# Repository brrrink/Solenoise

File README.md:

# Solenoise

## Overview

Solenoise is an open-source hardware and software system designed to transform everyday objects—such as metal plates, wooden surfaces, or architectural elements—into programmable percussive instruments. By leveraging solenoids as electromagnetic actuators, Solenoise enables automated performance, enhancing musical expressivity and extending human capabilities in experimental music, interactive installations, and architectural sound design.

The resurgence of analog modular synthesis, coupled with advancements in physical computing, has inspired this project. Traditional percussive instruments are limited by their fixed physical properties; Solenoise addresses this by providing a versatile control interface that bridges digital and physical realms.

## Key Features

- **Multi-Modal Input Control**: Supports class-compliant MIDI over TRS Mini-Jack, CV/gate inputs with internal logic for simplified and seamless integration with midi capable devices, modular synthesisers, and sequencers.
- **Hardware Simplicity**: Built around a Teensy 4.0 microcontroller with driverless MIDI input and simplified input protection circuits, ensuring compatibility with external devices.
- **Efficient Actuation**: Uses logic-level MOSFETs and protective transistors for safe and efficient operation of inductive loads (solenoids).
- **Configurable Software**: A flexible framework optimises latency and expressivity, with a focus on CV/Trigger input processing along with class compliant MIDI input.
- **Open-Source Ethos**: Unlike proprietary systems (e.g., Polyend Perc, Dada Machines Automat), Solenoise aims to democratise solenoid augmentation and aims to further collaborative innovation.

## Hardware Requirements

- **Microcontroller**: Teensy 4.0 (required for high-speed processing and MIDI support).
- **Solenoids**: Compatible 12V DC solenoids (e.g., push-pull types for striking objects).
- **Power Supply**: 12VDC Powers the development and the solenoids, with internal voltage protection and rectification.

### Input/Output

- **MIDI**: class-compliant MIDI (TRS Type A) via 3.175mm (1/8 inch) 'Mini Jack' input.
- **CV/Gate**: Analog inputs with protection circuits.

## Installation

- **Clone the repository**: git clone https://github.com/brrrink/Solenoise/solenoise.git
- cd solenoise
- Use Platformio to upload firmware to Teensy 4.0, hardware is available to purchase with pre-mounted SMD components or see the Solenoise Production Files folder, for all production ready design files.
- Upload these design files to the PCB manufacturer of your choice, who should be able to provide full soldered SMD PCB's from these files.
- A small number of through-hole components have to be added, these have been minimised to the degree possible to facilitate ease of construction.

## Usage

### Basic Setup

Attach solenoids to objects (e.g., via 3D-printed mounts—in progress enhancement).

Connect inputs:
- MIDI: Plug into a DAW or MIDI controller.
- Gates: Trigger via digital signals from sequencers.
- CV/Trigger: Use modular synth outputs for voltage-based control.

### Example: MIDI-Controlled Percussion

Send MIDI notes to Solenoise via Mini Jack (Type A).

### CV/Gate Integration

CV input controls the allocation of solenoid (12 in total)

Gate input will trigger discrete strikes, supplemented with MIDI for analog and moblie (battery powered) workflows.

### Performance Evaluation

Latency: <5ms for MIDI/CV processing (tested on Teensy 4.0).

Applications: Experimental music (e.g., hybrid human-robot performances), interactive art (e.g., responsive installations), sound design (e.g., architectural acoustics).

## Comparisons to Existing Systems

Solenoise builds on commercial and academic precedents but emphasises accessibility:

- **Commercial**: QRS PNOmation (piano retrofits), Polyend Perc (discontinued drumming machine), Dada Machines Automat (modular but costly), Koma Elektronik Field Kit (electroacoustic with solenoid control), Archil Lab Poet Pilot (object actuation).
- **Academic**: Logos Foundation <Vibi> (robotic vibraphone), Ajay Kapur's MahaDeviBot (percussion robot), Z-Machines guitar-bot.
- **Unique Aspects**: Open-source, CV/Gate inputs extend MIDI, driverless and mobile focussed design. 

## Future Enhancements

- 3D-printed solenoid mounts for easy attachment.
- Wireless control (e.g., via ESP32 integration).
- Expanded inputs/outputs for larger setups.
- Community-contributed presets and mappings.

## Contributing

Contributions are welcome! Fork the repo, create a branch, and submit a pull request. Focus areas:
- Bug fixes in firmware.
- New hardware variants (e.g., Eurorack compatibility).
- Documentation improvements.

Please follow the Code of Conduct.

## License

All non commercial use is approved.

Steal this code.

Commercial use is not approved without consent, contact the authour for more details: anon@anon.com

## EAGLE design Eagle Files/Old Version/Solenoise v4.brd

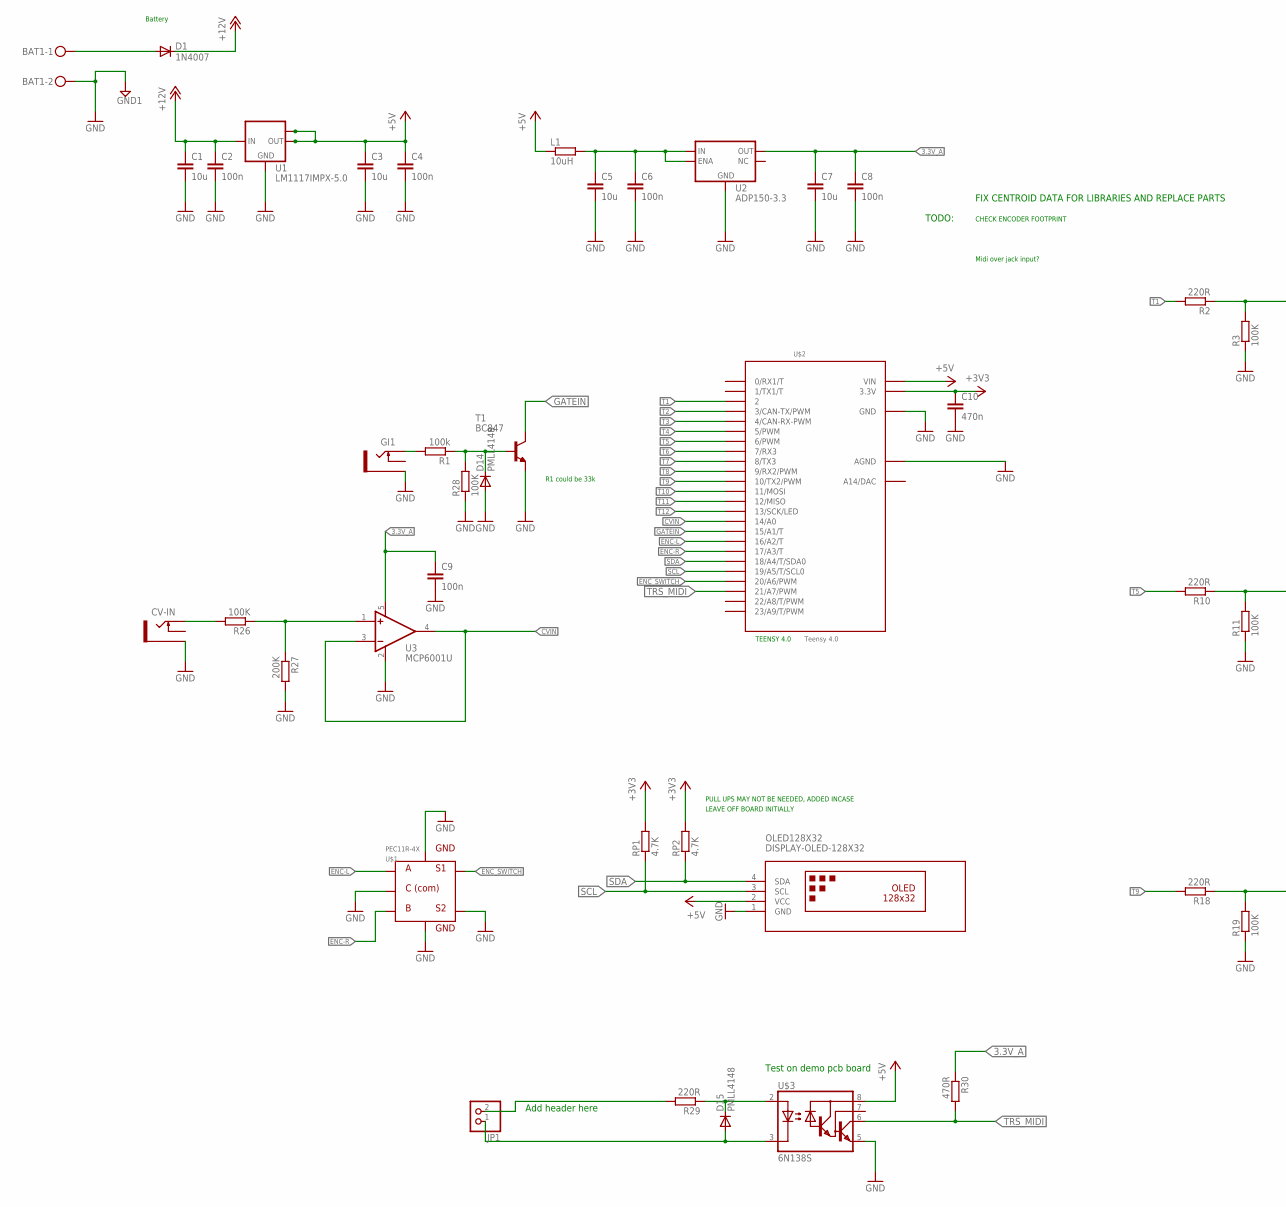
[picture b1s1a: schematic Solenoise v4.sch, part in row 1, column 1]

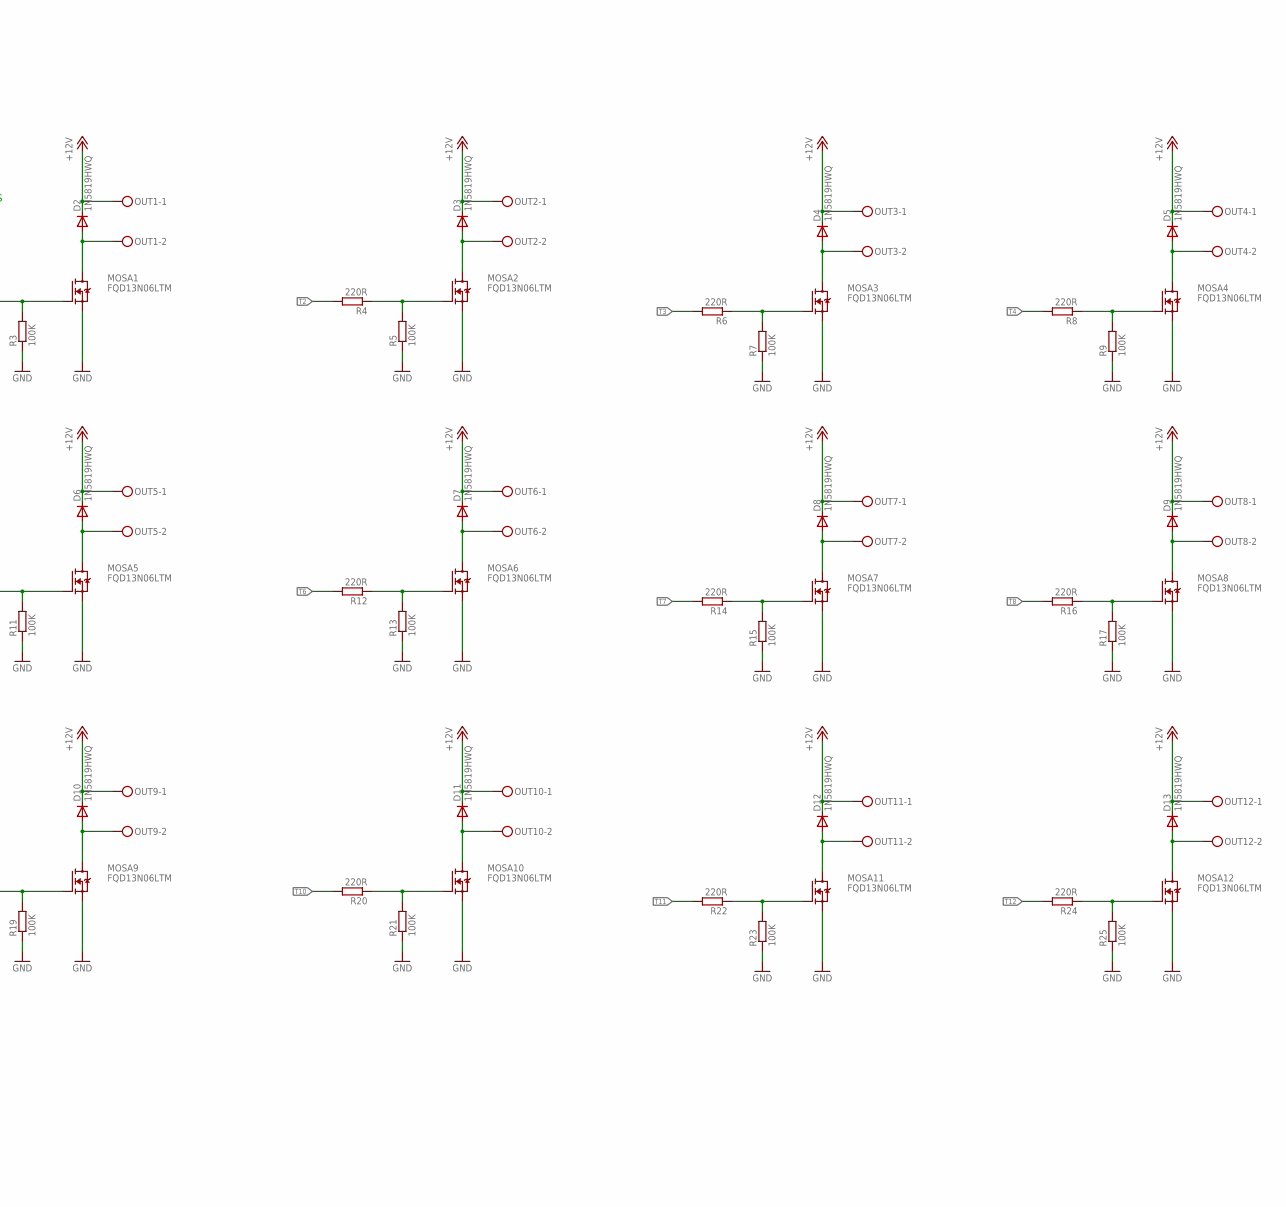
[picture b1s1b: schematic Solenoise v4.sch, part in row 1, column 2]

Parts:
BAT1: MKDSN1,5/2-5,08
C1, C3, C5, C7: 10u; C1206
C2, C4, C6, C8, C9: 100n; C0805
C10: 470n; C0805
CV-IN: THONKICONNNEW; WQP-PJ301M-12_JACK
D1: 1N4007; DO41-10
D2, D3, D4, D5, D6, D7, D8, D9, D10, D11, D12, D13: 1N5819HWQ; SOD123
D14, D15: PMLL4148; SOD80C
GI1: THONKICONNNEW; WQP-PJ301M-12_JACK
JP1: PINHD-1X2; 1X02
L1: 10uH; R0805
MOSA1, MOSA2, MOSA3, MOSA4, MOSA5, MOSA6, MOSA7, MOSA8, MOSA9, MOSA10, MOSA11, MOSA12: FQD13N06LTM
OLED128X32: DISPLAY-OLED-128X32
OUT1, OUT2, OUT3, OUT4, OUT5, OUT6, OUT7, OUT8, OUT9, OUT10, OUT11, OUT12: MKDSN1,5/2-5,08
R1: 100k; R0805
R2, R4, R6, R8, R10, R12, R14, R16, R18, R20, R22, R24, R29: 220R; R0805
R3, R5, R7, R9, R11, R13, R15, R17, R19, R21, R23, R25, R26, R28: 100K; R0805
R27: 200K; R0805
R30: 470R; R0805
RP1, RP2: 4.7K; R0805
T1: BC847; SOT23
U1: LM1117IMPX-5.0; SOT223
U2: ADP150-3.3; SOT23-5
U3: MCP6001U; MCP6001
U$1: PEC11R-4X; ENC
U$2: Teensy 4.0; TEENSY_3.1_DAC
U$3: 6N138S

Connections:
3.3V_A: C7.1, C8.1, C9.1, R30.1, U2.OUT (VOUT), U3.5 (V+)
+3V3: C10.1, RP1.2, RP2.2, U$2.3.3V
+5V: C3.1, C4.1, L1.1, OLED128X32.2 (VCC), U1.2 (OUT), U1.TAB (OUT1), U$2.VIN, U$3.8 (VCC)
+12V: C1.1, C2.1, D1.C, D2.C, D3.C, D4.C, D5.C, D6.C, D7.C, D8.C, D9.C, D10.C, D11.C, D12.C, D13.C, OUT1.1, OUT2.1, OUT3.1, OUT4.1, OUT5.1, OUT6.1, OUT7.1, OUT8.1, OUT9.1, OUT10.1, OUT11.1, OUT12.1, U1.3 (IN)
CVIN: U3.3 (-IN), U3.4 (OUT), U$2.14/A0
ENC-L: U$1.A, U$2.16/A2 (16/A2/T)
ENC-R: U$1.B, U$2.17/A3 (17/A3/T)
ENC_SWITCH: U$1.1 (SW1), U$2.20/A6 (20/A6/PWM)
GATEIN: T1.3 (C), U$2.15/A1 (15/A1/T)
GND: BAT1.2, C1.2, C2.2, C3.2, C4.2, C5.2, C6.2, C7.2, C8.2, C9.2, C10.2, CV-IN.P$3_SLEEVE (SLEEVE), D14.A, GI1.P$3_SLEEVE (SLEEVE), MOSA1.2 (S), MOSA2.2 (S), MOSA3.2 (S), MOSA4.2 (S), MOSA5.2 (S), MOSA6.2 (S), MOSA7.2 (S), MOSA8.2 (S), MOSA9.2 (S), MOSA10.2 (S), MOSA11.2 (S), MOSA12.2 (S), OLED128X32.1 (GND), R3.1, R5.1, R7.1, R9.1, R11.1, R13.1, R15.1, R17.1, R19.1, R21.1, R23.1, R25.1, R27.2, R28.1, T1.2 (E), U1.1 (GND), U2.GND, U3.2 (V-), U$1.2 (SW2), U$1.C, U$1.GND1, U$1.GND2, U$2.AGND, U$2.GND, U$3.5 (GND)
MOS1.1: D2.A, MOSA1.3 (D), OUT1.2
MOS1.2: D3.A, MOSA2.3 (D), OUT2.2
MOS1.3: D4.A, MOSA3.3 (D), OUT3.2
MOS1.4: D5.A, MOSA4.3 (D), OUT4.2
MOS1.5: D6.A, MOSA5.3 (D), OUT5.2
MOS1.6: D7.A, MOSA6.3 (D), OUT6.2
MOS1.7: D8.A, MOSA7.3 (D), OUT7.2
MOS1.8: D9.A, MOSA8.3 (D), OUT8.2
MOS1.9: D10.A, MOSA9.3 (D), OUT9.2
MOS1.10: D11.A, MOSA10.3 (D), OUT10.2
MOS1.11: D12.A, MOSA11.3 (D), OUT11.2
MOS1.12: D13.A, MOSA12.3 (D), OUT12.2
unnamed: R26.1, R27.1, U3.1 (+IN)
unnamed: MOSA1.1 (G), R2.1, R3.2
unnamed: MOSA2.1 (G), R4.1, R5.2
unnamed: MOSA3.1 (G), R6.1, R7.2
unnamed: CV-IN.P$1_TIP (TIP), R26.2
unnamed: C5.1, C6.1, L1.2, U2.EN (ENA), U2.VIN (IN)
unnamed: MOSA4.1 (G), R8.1, R9.2
unnamed: MOSA5.1 (G), R10.1, R11.2
unnamed: MOSA6.1 (G), R12.1, R13.2
unnamed: MOSA7.1 (G), R14.1, R15.2
unnamed: MOSA8.1 (G), R16.1, R17.2
unnamed: MOSA9.1 (G), R18.1, R19.2
unnamed: MOSA10.1 (G), R20.1, R21.2
unnamed: MOSA11.1 (G), R22.1, R23.2
unnamed: MOSA12.1 (G), R24.1, R25.2
unnamed: BAT1.1, D1.A
unnamed: GI1.P$1_TIP (TIP), R1.2
unnamed: D14.C, R1.1, R28.2, T1.1 (B)
unnamed: D15.C, R29.1, U$3.2 (A)
unnamed: D15.A, JP1.1, U$3.3 (C)
unnamed: JP1.2, R29.2
SCL: OLED128X32.3 (SCL), RP1.1, U$2.19/A5 (19/A5/T/SCL0)
SDA: OLED128X32.4 (SDA), RP2.1, U$2.18/A4 (18/A4/T/SDA0)
T1: R2.2, U$2.2
T2: R4.2, U$2.3 (3/CAN-TX/PWM)
T3: R6.2, U$2.4 (4/CAN-RX-PWM)
T4: R8.2, U$2.5 (5/PWM)
T5: R10.2, U$2.6 (6/PWM)
T6: R12.2, U$2.7 (7/RX3)
T7: R14.2, U$2.8 (8/TX3)
T8: R16.2, U$2.9 (9/RX2/PWM)
T9: R18.2, U$2.10 (10/TX2/PWM)
T10: R20.2, U$2.11 (11/MOSI)
T11: R22.2, U$2.12 (12/MISO)
T12: R24.2, U$2.13 (13/SCK/LED)
TRS_MIDI: R30.2, U$2.21/A7 (21/A7/PWM), U$3.6 (VO)

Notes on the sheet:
TODO:
R1 could be 33k
PULL UPS MAY NOT BE NEEDED, ADDED INCASE
LEAVE OFF BOARD INITIALLY
CHECK ENCODER FOOTPRINT
TEENSY 4.0
Battery
Midi over jack input?
FIX CENTROID DATA FOR LIBRARIES AND REPLACE PARTS
Add header here
Test on demo pcb board

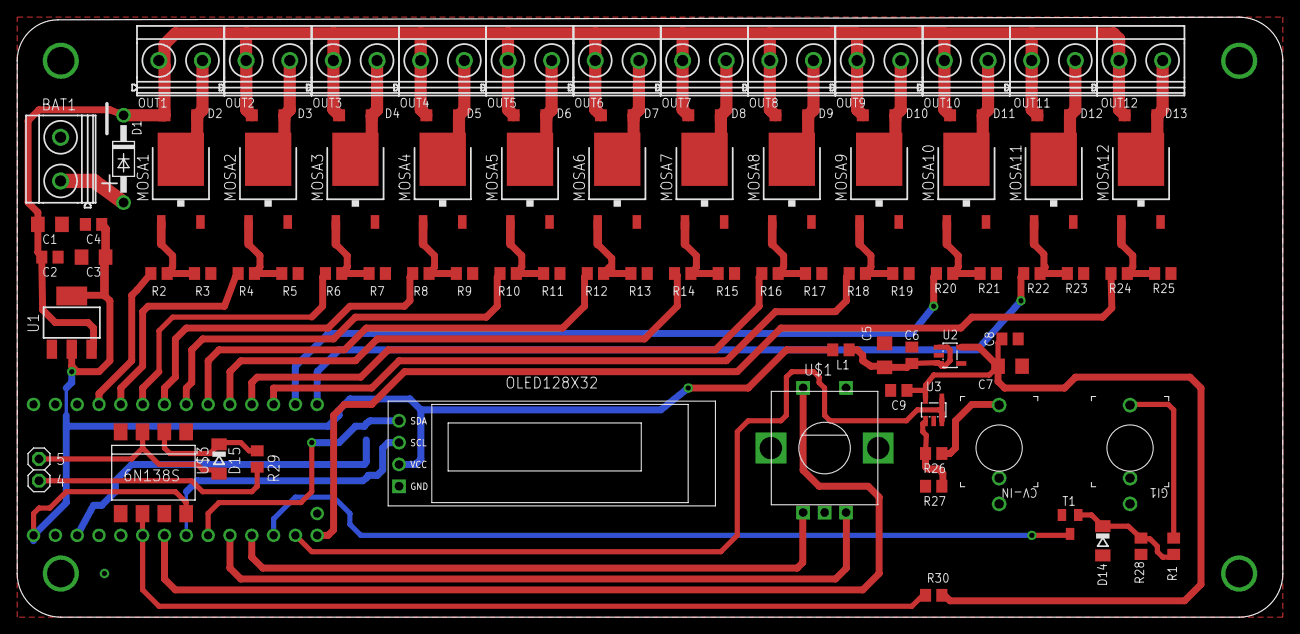
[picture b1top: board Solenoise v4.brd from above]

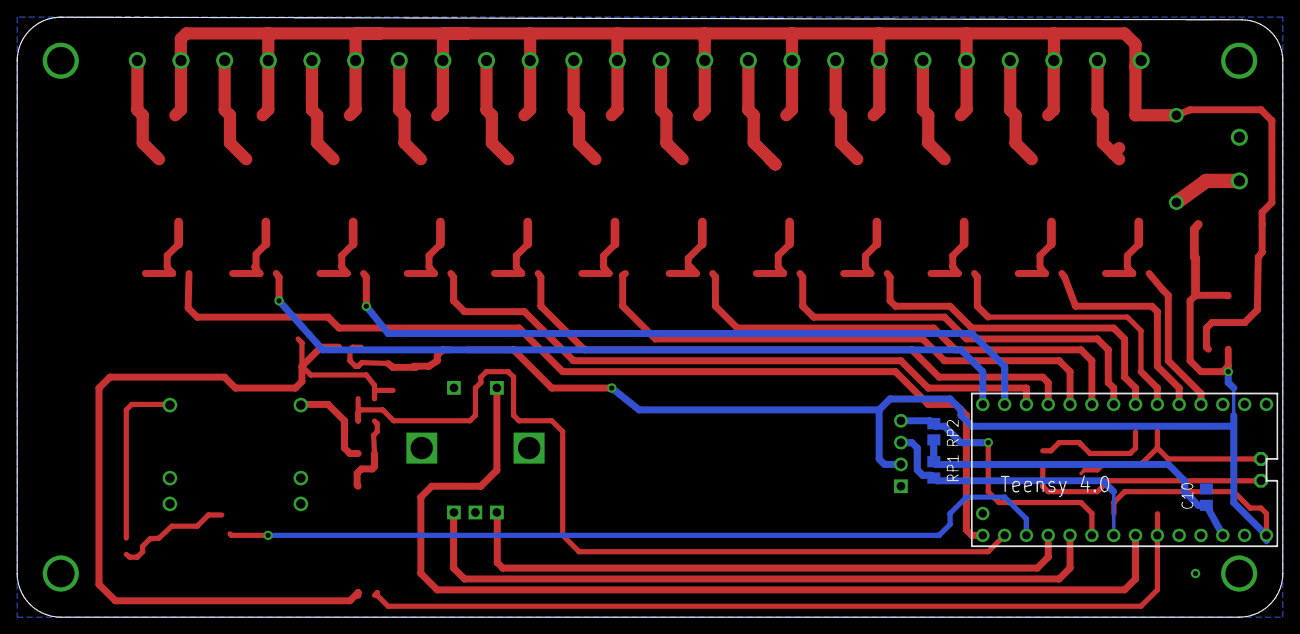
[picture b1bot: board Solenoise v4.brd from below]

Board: 2 copper layers, 147.3 x 69.8 mm, 94 parts (4 on the bottom side), 58 nets.

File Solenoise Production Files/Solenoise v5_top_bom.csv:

Qty,Designator,Footprint,Comment,LCSC #
4,"C1, C3, C5, C7",C1206,10u,C77092
6,"C2, C4, C6, C8, C9, C11",C0805,100n,C28233
1,C10,C0805,470n,C13967
12,"D2, D3, D4, D5, D6, D7, D8, D9, D10, D11, D12, D13",SOD123,1N5819HWQ,C460770
2,"D14, D15",SOD80C,PMLL4148,C78613
1,L1,R0805,10uH,C223171
12,"MOSA1, MOSA2,MOSA3, MOSA4, MOSA5, MOSA6, MOSA7, MOSA8, MOSA9, MOSA10, MOSA11, MOSA12",FQD13N06LTM,FQD13N06LTM,C236914
15,"R1, R3, R5, R7, R9, R11,R13, R15, R17, R19, R21, R23, R25, R26, R28",R0805,100k,C96346
13,"R2, R4, R6, R8, R10, R12, R14, R16, R18, R20, R22, R24, R29",R0805,220R,C114519
1,R30,R0805,470R,C114564
1,R27,R0805,200K,C114235
1,T1,SOT23,BC847,C8664
1,U$3,SO-6-5,TLP2361,C6285467
1,U1,SOT223,LM1117IMPX-5.0,C41202
1,U2,SOT23-5,ADP150-3.3,C29149
1,U3,MCP6001,MCP6001U,C21403

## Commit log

2026-06-16 Pushing CV/Gate initial firmware
2026-06-16 Reorganising old firmware
2026-06-17 Add new Firmware versions

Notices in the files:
parts and their libraries:
OLED: Released under the Creative Commons Attribution 4.0 International License: http://creativecommons.org/licenses/by/4.0
